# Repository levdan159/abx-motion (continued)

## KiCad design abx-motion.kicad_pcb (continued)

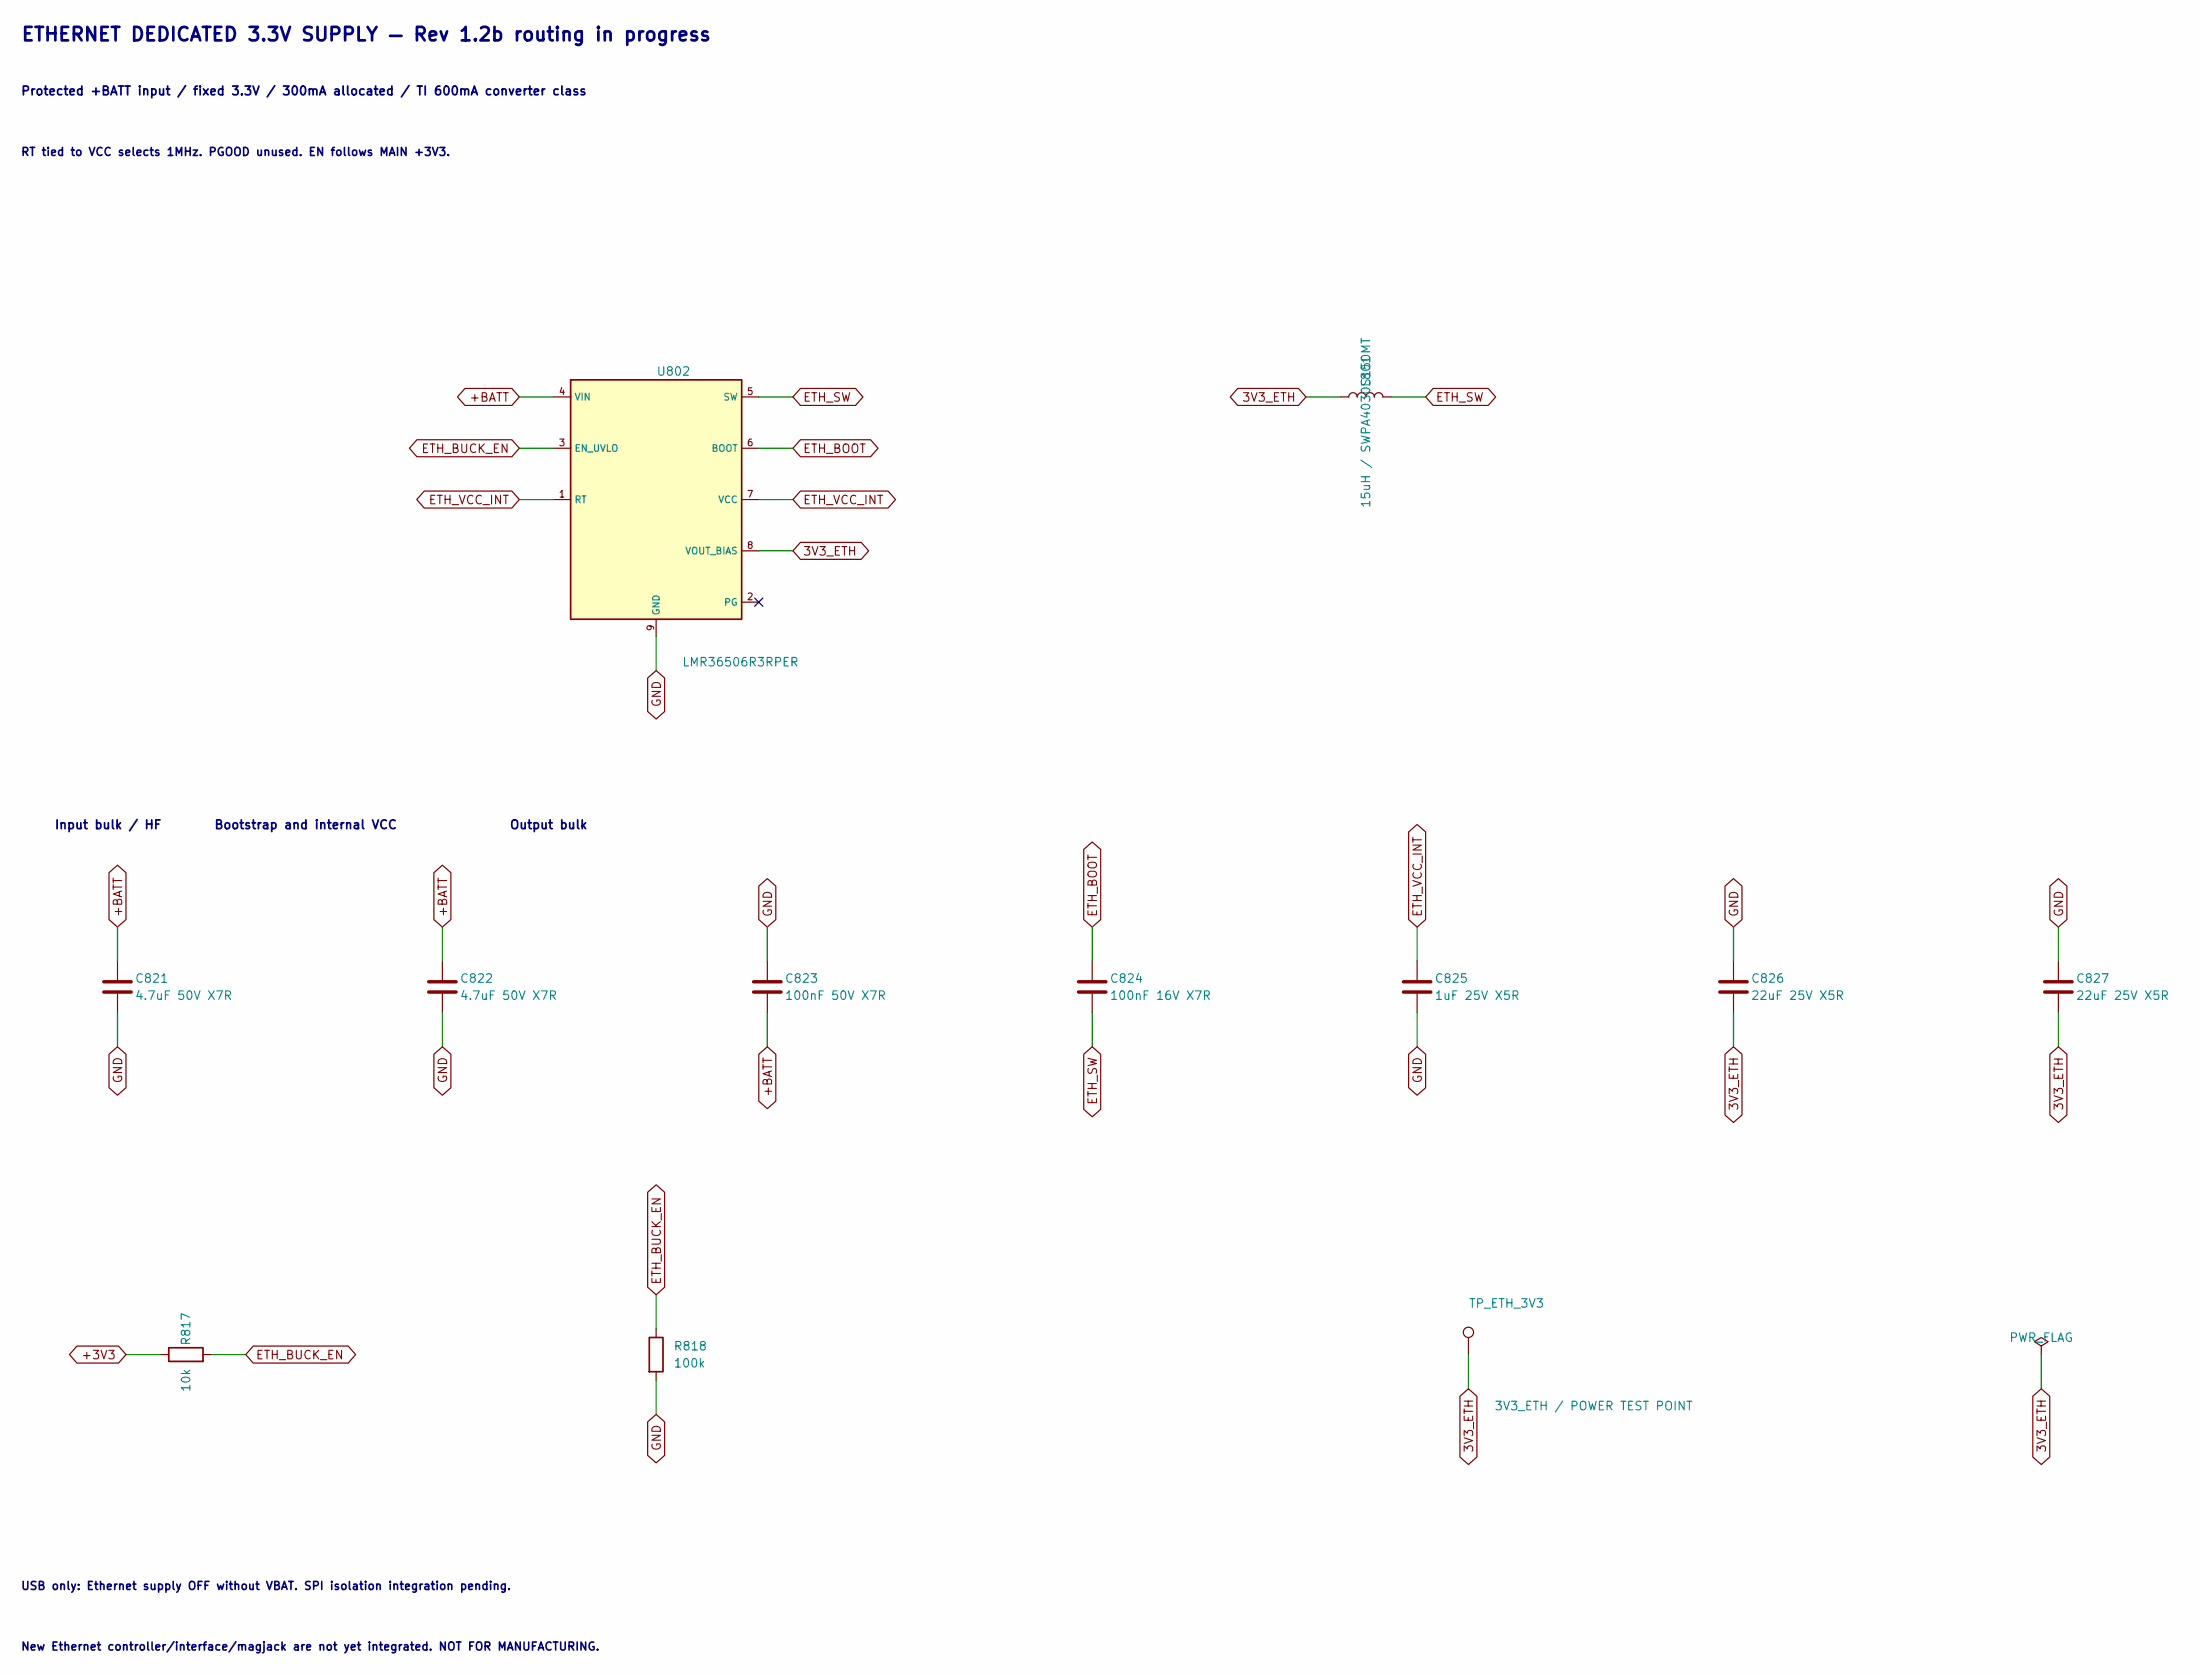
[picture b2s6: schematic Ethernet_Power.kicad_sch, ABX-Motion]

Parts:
C821, C822: 4.7uF 50V X7R; C_1206_3216Metric
C823: 100nF 50V X7R; C_0603_1608Metric
C824: 100nF 16V X7R; C_0402_1005Metric
C825: 1uF 25V X5R; C_0402_1005Metric
C826, C827: 22uF 25V X5R; C_1206_3216Metric
L801: 15uH / SWPA4030S150MT; L_Sunlord_SWPA4030S
R817: 10k; R_0402_1005Metric
R818: 100k; R_0402_1005Metric
TP_ETH_3V3: 3V3_ETH / POWER TEST POINT; TestPoint_Pad_D1.5mm
U802: LMR36506R3RPER; LMR36506_RPE0009B

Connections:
3V3_ETH: C826.2, C827.2, L801.1, TP_ETH_3V3.1, U802.8 (VOUT_BIAS)
+3V3: R817.1; also elsewhere on the board
ETH_BOOT: C824.1, U802.6 (BOOT)
ETH_BUCK_EN: R817.2, R818.1, U802.3 (EN_UVLO)
ETH_SW: C824.2, L801.2, U802.5 (SW)
ETH_VCC_INT: C825.1, U802.1 (RT), U802.7 (VCC)

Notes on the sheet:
ETHERNET DEDICATED 3.3V SUPPLY — Rev 1.2b routing in progress
Protected +BATT input / fixed 3.3V / 300mA allocated / TI 600mA converter class
RT tied to VCC selects 1MHz. PGOOD unused. EN follows MAIN +3V3.
Input bulk / HF Bootstrap and internal VCC Output bulk
USB only: Ethernet supply OFF without VBAT. SPI isolation integration pending.
New Ethernet controller/interface/magjack are not yet integrated. NOT FOR MANUFACTURING.

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
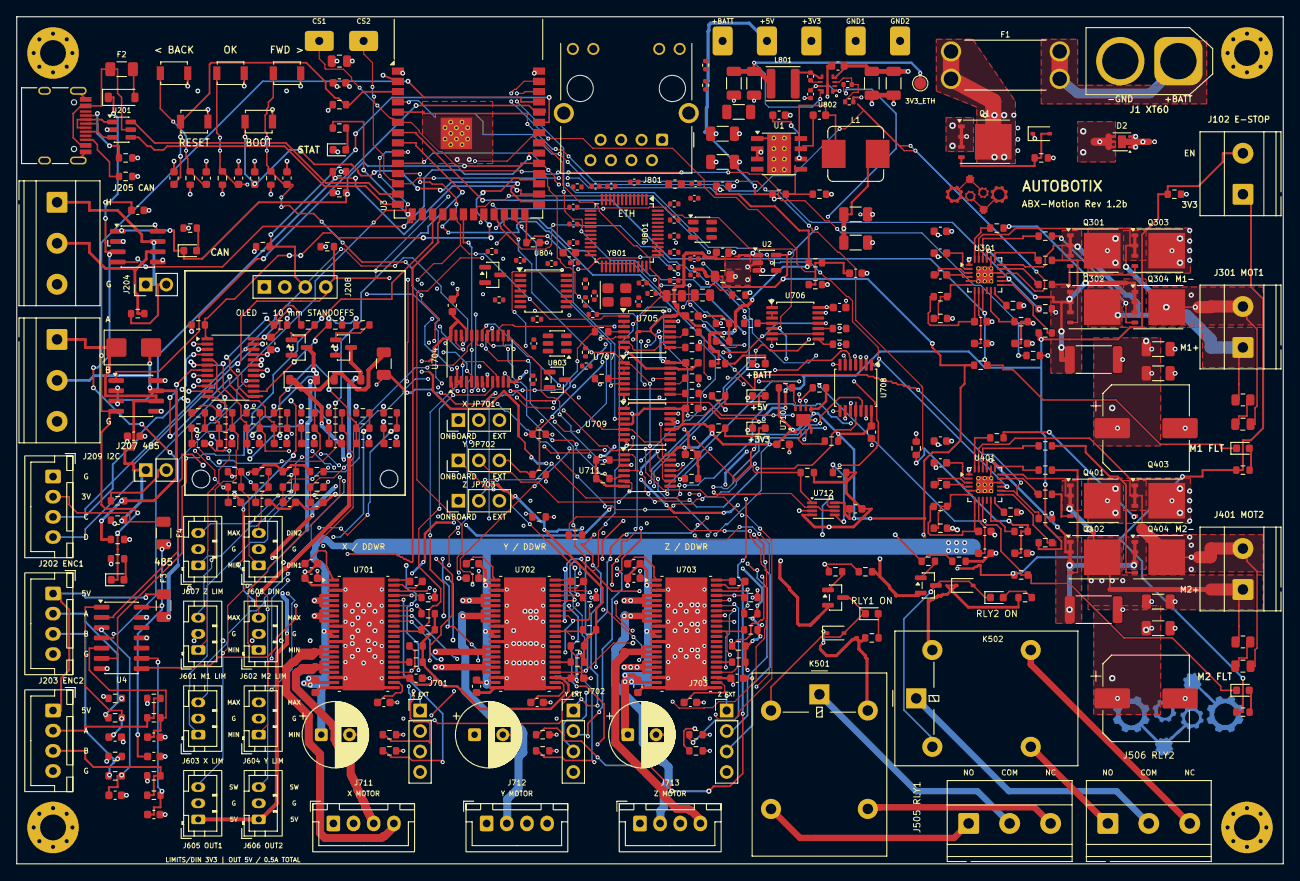
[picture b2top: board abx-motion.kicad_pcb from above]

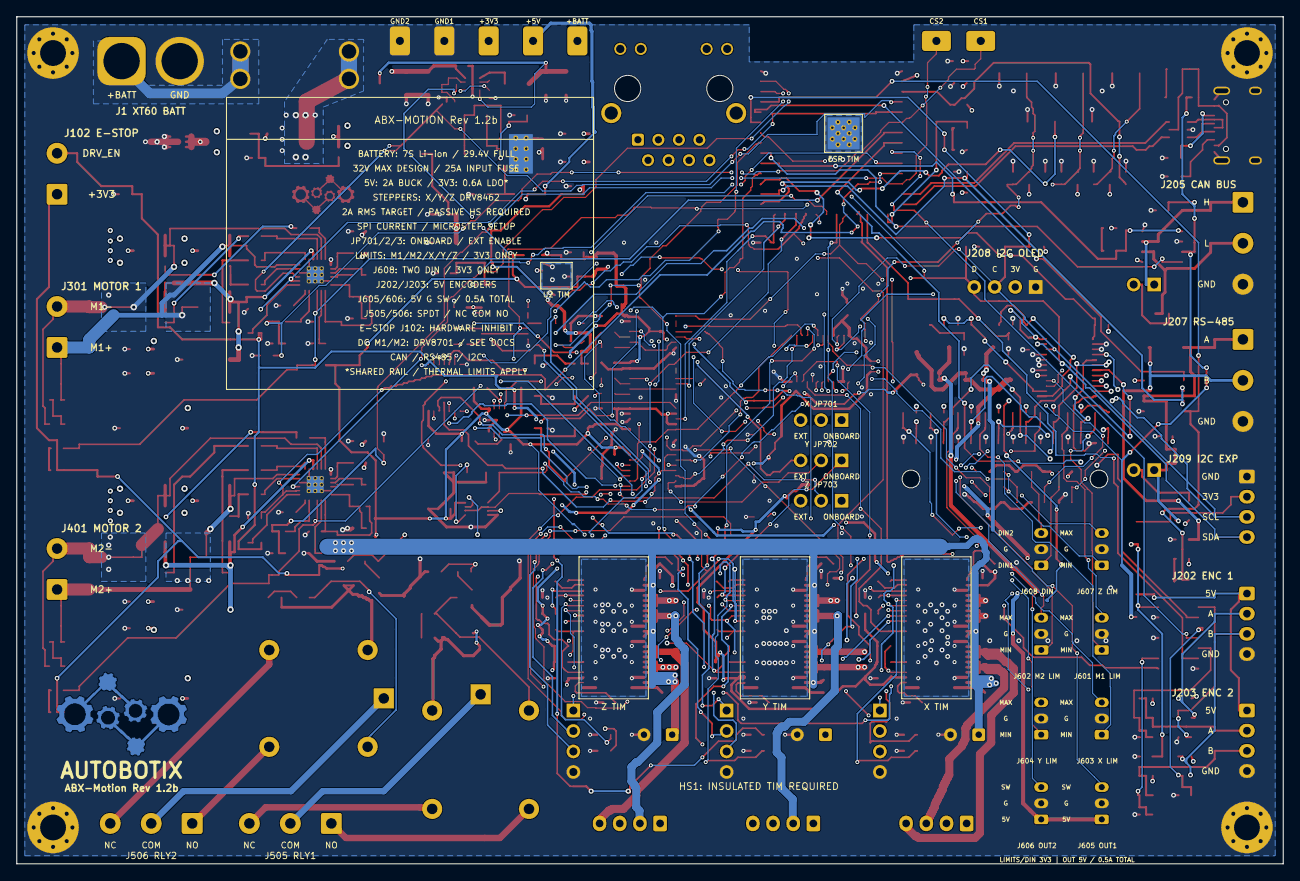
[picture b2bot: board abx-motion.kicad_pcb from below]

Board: 4 copper layers, 157.0 x 105.0 mm, 406 parts (2 on the bottom side), 254 nets.

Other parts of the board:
C5: 1uF; C_0603_1608Metric
C801, C802, C803, C804, C805, C806, C807, C815, C819, C828, C829: 100nF; C_0402_1005Metric
C809: 4.7uF; C_0603_1608Metric
C810, C816: 10nF; C_0402_1005Metric
C811, C812: 10uF; C_0805_2012Metric
C813, C814: CL TBD; C_0402_1005Metric
C817, C818: 6.8nF; C_0402_1005Metric
C820: 1nF HV / SELECT; C_1206_3216Metric
D801: ETHERNET ESD / SELECT; SOT-23-6
FB801: FERRITE / RATED >=300mA; L_0603_1608Metric
J801: HR911105A / C12074; RJ45_Hanrun_HR911105A_Horizontal
Q801, Q802: BSS138; SOT-23
R801: 12.4k 1%; R_0402_1005Metric
R802, R803, R804, R805: 49.9R 1%; R_0402_1005Metric
R806, R807, R808, R809, R810, R819, R821: 10k; R_0402_1005Metric
R811, R812: 330R; R_0402_1005Metric
R813, R814, R815: 22R / SI TBD; R_0402_1005Metric
R816: 100k; R_0402_1005Metric
R820: 4.7k; R_0402_1005Metric
TIM_ESP: GND TIM 4x4 NO PASTE; TIM_GND_4x4_Bottom
U801: W5500 / C32843; LQFP-48_7x7mm_P0.5mm
U803: TPS3808G33DBVR; SOT-23-6
U804: TXU0304PWR; TSSOP-14_4.4x5mm_P0.65mm
Y801: 25MHz / CL TO SELECT; ABX_Y801_Crystal_SMD_3225-4Pin_3.2x2.5mm

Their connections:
/Power_Supply/U1_VCC: C5.1; also elsewhere on the board

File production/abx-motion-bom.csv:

Comment,Designator,Footprint,LCSC Part #
100nF,"C1,C4,C6,C202,C203,C204,C209,C210,C211,C212,C213,C214,C302,C309,C402,C409,C601",C_0603_1608Metric,C14663
4.7uF,"C2,C3,C307,C308,C407,C408",C_1206_3216Metric,C29823
1uF,"C5,C9,C301,C303,C304,C401,C403,C404",C_0603_1608Metric,C15849
22uF,"C7,C8",C_1206_3216Metric,C12891
10uF,"C10,C201",C_0805_2012Metric,C15850
1nF,"C205,C206,C207,C208",C_0603_1608Metric,C1588
10nF,"C305,C405,C602,C603,C604,C605,C606,C607,C608,C609",C_0603_1608Metric,C57112
220uF,"C306,C406",CP_Elec_10x10.5,C72499
2.2nF,"C310,C410",C_0805_2012Metric,C107136
100uF,"C501,C502",CP_Elec_8x10.5,C72480
BZT52C12S,D1,D_SOD-323,C14643
SMCJ30A,D2,D_SMC,C310046
SMBJ6.5CA,D201,D_SMB,C78428
B5819W,"D202,D601,D602",D_SOD-123,C8598
1N4148WS,"D501,D503",D_SOD-323,C2128
LED_GRN,"D502,D504,LED_PWR_3V3_1,LED_PWR_5V1,LED_PWR_BATT1",LED_0603_1608Metric,C12624
25A,F1,Fuseholder_Keystone_3557-2,C352820
500mA_PTC,"F2,F3",Fuse_1206_3216Metric,C2984676
250mA_PTC,F4,Fuse_1206_3216Metric,C20798
500mA_PTC,F5,Fuse_1206_3216Metric,C70125
XT60_BAT,J1,AMASS_XT60-M_1x02_P7.20mm_Vertical,C98733
E_STOP,J102,"TerminalBlock_Phoenix_MKDS-1,5-2-5.08_1x02_P5.08mm_Horizontal",C8465
USB-C,J201,USB_C_Receptacle_HRO_TYPE-C-31-M-12,C165948
ENC1_CONN,J202,JST_XH_B4B-XH-A_1x04_P2.50mm_Vertical,C566014
ENC2_CONN,J203,JST_XH_B4B-XH-A_1x04_P2.50mm_Vertical,C566014
CAN_TERM,J204,PinHeader_1x02_P2.54mm_Vertical,C492401
CAN_BUS,J205,"TerminalBlock_Phoenix_MKDS-1,5-3-5.08_1x03_P5.08mm_Horizontal",C72334
RS485_TERM,J206,PinHeader_1x02_P2.54mm_Vertical,C492401
RS485_BUS,J207,"TerminalBlock_Phoenix_MKDS-1,5-3-5.08_1x03_P5.08mm_Horizontal",C72334
OLED_I2C,J208,PinSocket_1x04_P2.54mm_Vertical,C2718488
I2C_EXP,J209,JST_XH_B4B-XH-A_1x04_P2.50mm_Vertical,C566014
MOTOR_OUT,"J301,J401","TerminalBlock_Phoenix_MKDS-1,5-2-5.08_1x02_P5.08mm_Horizontal",C8465
STEP1_MOTOR,J501,JST_XH_B4B-XH-A_1x04_P2.50mm_Vertical,C566014
STEP1_EXT,J502,JST_XH_B4B-XH-A_1x04_P2.50mm_Vertical,C566014
STEP2_MOTOR,J503,JST_XH_B4B-XH-A_1x04_P2.50mm_Vertical,C566014
STEP2_EXT,J504,JST_XH_B4B-XH-A_1x04_P2.50mm_Vertical,C566014
RELAY1_OUT,J505,"TerminalBlock_Phoenix_MKDS-1,5-3-5.08_1x03_P5.08mm_Horizontal",C72334
RELAY2_OUT,J506,"TerminalBlock_Phoenix_MKDS-1,5-3-5.08_1x03_P5.08mm_Horizontal",C72334
B3B-PH-K-S,"J601,J602,J603,J604,J605,J606",JST_PH_B3B-PH-K_1x03_P2.00mm_Vertical,C131339
G5LE-14-DC5,"K501,K502",Relay_SPDT_Omron-G5LE-1,C116963
15uH,L1,L_Bourns_SRP7028A_7.3x6.6mm,C177243
LED_YEL_CAN,LED201,LED_0603_1608Metric,C2287
LED_YEL_485,LED202,LED_0603_1608Metric,C2287
LED_BLU_STAT,LED203,LED_0603_1608Metric,C2288
LED_RED_FLT,"LED_FLT1,LED_FLT2",LED_0603_1608Metric,C2286
SQJ459EP-T1_GE3,Q1,TDSON-8-1,C3289501
CSD18540Q5B,"Q301,Q302,Q303,Q304,Q401,Q402,Q403,Q404",TDSON-8-1,C86513
AO3400A,"Q501,Q502,Q503,Q504,Q601,Q602",SOT-23,C20917
47k,R1,R_0603_1608Metric,C25819
100k,"R2,R4",R_0603_1608Metric,C25803
10k,"R3,R6,R9,R203,R204,R205,R206,R207,R208,R209,R210,R227,R228,R229,R231,R232,R303,R403,R505,R506,R507,R508,R621,R622",R_0603_1608Metric,C25804
24.9k,R5,R_0603_1608Metric,C25962
1k,"R7,R8,R212,R214,R216,R218,R220,R224,R230,R304,R311,R404,R411,R502,R504,R609,R610,R611,R612,R613,R614,R615,R616,R617,R618",R_0603_1608Metric,C21190
5.1k,"R201,R202",R_0603_1608Metric,C23186
4.7k,"R211,R213,R215,R217,R225,R226,R601,R602,R603,R604,R605,R606,R607,R608",R_0603_1608Metric,C23162
120,"R219,R221",R_0603_1608Metric,C22787
330R,"R222,R223",R_0603_1608Metric,C23138
18k,"R301,R401",R_0603_1608Metric,C25810
30k,"R302,R402",R_0603_1608Metric,C22984
10,"R305,R306,R307,R308,R405,R406,R407,R408",R_0603_1608Metric,C22859
10mR_3W,"R309,R409",R_2512_6332Metric,C840621
10,"R310,R410",R_0805_2012Metric,C844598
200k,"R312,R412",R_0603_1608Metric,C25811
100,"R501,R503,R619,R620",R_0603_1608Metric,C22775
RESET,SW201,SW_SPST_B3U-1000P,C231329
BOOT,SW202,SW_SPST_B3U-1000P,C231329
BTN_BACK,SW203,SW_SPST_B3U-1000P,C231329
BTN_NEXT,SW204,SW_SPST_B3U-1000P,C231329
BTN_HOME,SW205,SW_SPST_B3U-1000P,C231329
MICROSTEP_CFG,"SW501,SW502",SW_DIP_SPSTx03_Slide_9.78x9.8mm_W8.61mm_P2.54mm,C319040
LMR36520FADDA,U1,Texas_HSOP-8-1EP_3.9x4.9mm_P1.27mm_ThermalVias,C1858395
AP2112K-3.3,U2,SOT-23-5,C51118
ESP32-S3-WROOM-1-N8R2,U3,ESP32-S3-WROOM-1,C2913204
74LVC14A,U4,SOIC-14_3.9x8.7mm_P1.27mm,C133541
USBLC6-2SC6,U201,SOT-23-6,C7519
TCAN1042V-Q1,U202,SOIC-8_3.9x4.9mm_P1.27mm,C132550
THVD1450DR,U203,SOIC-8_3.9x4.9mm_P1.27mm,C2671361
DRV8701ERGER,"U301,U401",Texas_RGE0024C_VQFN-24-1EP_4x4mm_P0.5mm_EP2.1x2.1mm_ThermalVias,C90964
PinSocket_1x08,"U501_L,U501_R,U502_L,U502_R",PinSocket_1x08_P2.54mm_Vertical,C145755
"PCA9555PW,118",U601,TSSOP-24_4.4x7.8mm_P0.65mm,C128392

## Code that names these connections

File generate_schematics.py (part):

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    sb.stub_net(u3, "27", "ESP_BOOT", length=7.62)
    sb.stub_net(u3, "39", "VBAT_SENSE", length=7.62, hier_shape="input")
    sb.stub_net(u3, "38", "M2_nFAULT", length=7.62, hier_shape="input")
    sb.stub_net(u3, "15", "LED_STAT", length=7.62)  # GPIO 3 Heartbeat LED
    sb.stub_net(u3, "4", "M1_PWM_PH", length=7.62, hier_shape="output")
    sb.stub_net(u3, "5", "M1_PWM_EN", length=7.62, hier_shape="output")
    sb.stub_net(u3, "6", "M1_CS", length=7.62, hier_shape="input")
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    sb.stub_net(u3, "9", "ENC1_B", length=7.62)

    # Right side pins of U3 (All expansion pins connected!)
    sb.stub_net(u3, "37", "RS485_TX", length=7.62)      # GPIO 43 (TXD0)
    sb.stub_net(u3, "36", "RS485_RX", length=7.62)      # GPIO 44 (RXD0)
    sb.stub_net(u3, "10", "M2_PWM_PH", length=7.62, hier_shape="output")
    sb.stub_net(u3, "11", "M2_PWM_EN", length=7.62, hier_shape="output")
    sb.stub_net(u3, "13", "USB_DN", length=7.62)
    sb.stub_net(u3, "14", "USB_DP", length=7.62)
    sb.stub_net(u3, "23", "BTN_BACK", length=7.62)      # GPIO 21 (moved from GPIO 36)
    sb.stub_net(u3, "28", "RS485_DIR", length=7.62)     # GPIO 35
    sb.stub_net(u3, "29", "IO_INT_N", length=7.62, hier_shape="input")  # GPIO 36 (~INT from PCA9555PW)
    sb.stub_net(u3, "30", "BTN_NEXT", length=7.62)      # GPIO 37
    sb.stub_net(u3, "31", "CAN_TX", length=7.62)        # GPIO 38
    sb.stub_net(u3, "32", "CAN_RX", length=7.62)        # GPIO 39
    sb.stub_net(u3, "33", "BTN_HOME", length=7.62)      # GPIO 40
    sb.stub_net(u3, "34", "I2C_SDA", length=7.62, hier_shape="bidirectional")  # GPIO 41
    sb.stub_net(u3, "35", "I2C_SCL", length=7.62, hier_shape="output")         # GPIO 42
    sb.no_conn(u3, "26")                                # IO45 strapping pin unused
    sb.no_conn(u3, "16")                                # IO46 strapping pin unused
    sb.stub_net(u3, "24", "RELAY_1", length=7.62, hier_shape="output")
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    for gpin in ["S1", "A1", "A12", "B1", "B12"]:
        sb.stub_power(j201, gpin, "GND")
    for vpin in ["A4", "A9", "B4", "B9"]:
        sb.stub_net(j201, vpin, "VBUS_USB", length=6.35)
    sb.stub_net(j201, "A5", "USB_CC1", length=6.35)
    sb.stub_net(j201, "B5", "USB_CC2", length=6.35)
    sb.stub_net(j201, "A7", "USB_CONN_DN", length=6.35)
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    sb.stub_net(r219, "1", "CAN_TERM_SW")
    sb.stub_net(r219, "2", "CAN_L")

    # CAN 3-Pin 5.08mm Terminal J205 (CAN_H, CAN_L, GND)
    j205 = sb.place_sym(
        "Connector:Conn_01x03_Pin",
        "J205",
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    sb.stub_net(r223, "1", "RS485_B")
    sb.stub_power(r223, "2", "GND")

    # TVS Diode D201 across RS485_A and RS485_B + 3-Pin 5.08mm Terminal J207 (A, B, GND)
    d201 = sb.place_sym("Device:D_TVS", "D201", "SMBJ6.5CA", "Diode_SMD:D_SMB", 241.3, 264.16, 90)
    sb.stub_net(d201, "1", "RS485_A")
    sb.stub_net(d201, "2", "RS485_B")
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        sb.stub_net(sw_b, "1", btn_net)
        sb.stub_power(sw_b, "2", "GND")

    # 5. Heartbeat LED203 (Blue) + 1k Resistor R230 on GPIO 3 (LED_STAT)
    r230 = sb.place_sym("Device:R", "R230", "1k", "Resistor_SMD:R_0603_1608Metric", 35.56, 185.42, 0)
    sb.stub_net(r230, "1", "LED_STAT")
    sb.stub_net(r230, "2", "STAT_LED_A")
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    sb.stub_net(udrv, "12", "DRV_IDRIVE", length=7.62)  # Configurable IDRIVE via 200k R312/R412 to GND
    sb.stub_power(udrv, "5", "GND", length=7.62)   # AGND

    # R12 (R312 / R412): 200k 0603 from DRV_IDRIVE (Pin 12) to GND -> 25mA/50mA gate drive & bench-tunable
    r, alt = mref("R12")
    r_idrv = sb.place_sym("Device:R", r, "200k", "Resistor_SMD:R_0603_1608Metric", 198.12, 175.26, 0, alt_refs=alt)
    sb.stub_net(r_idrv, "1", "DRV_IDRIVE")
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    sb.stub_net(udrv, "24", "GH2_RAW", length=7.62)
    sb.stub_net(udrv, "23", "MOT_OUT2", length=7.62)
    sb.stub_net(udrv, "22", "GL2_RAW", length=7.62)
    sb.stub_net(udrv, "21", "SHUNT_SP", length=7.62)  # Pin 21 (SP) -> low-side MOSFET source node (top of R309)
    sb.stub_power(udrv, "20", "GND", length=7.62)     # Pin 20 (SN) -> GND Kelvin side of R309
    sb.stub_net(udrv, "11", "SO_RAW", length=7.62)
    sb.stub_net(udrv, "9", "nFAULT", length=7.62, hier_shape="output")
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    sb.stub_power(udrv, "25", "GND", length=7.62)  # EP

    # Charge pump & regulator passives:
    # CRITICAL: C01 (1uF 16V) from VCP (Pin 2) to VM (+BATT), NOT GND!
    r, alt = mref("C01")
    c_vcp = sb.place_sym("Device:C", r, "1uF", "Capacitor_SMD:C_0603_1608Metric", 38.1, 149.86, 0, alt_refs=alt)
    sb.stub_power(c_vcp, "1", "+BATT")
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        sb.stub_power(j_out, "2", "GND")
        sb.stub_net(j_out, "3", f"OUT{ch}_SW")

    # 4. Independent Stepper Enables (IO1_2=Pin 15 -> STEP1_EN, IO1_3=Pin 16 -> STEP2_EN) with 10k pull-ups R621, R622 to +3V3 & ESTOP_SENSE (IO1_4=Pin 17)
    sb.stub_net(u601, "15", "STEP1_EN", length=7.62, hier_shape="output")
    sb.stub_net(u601, "16", "STEP2_EN", length=7.62, hier_shape="output")

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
